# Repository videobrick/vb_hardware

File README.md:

hardware
========

OSHW Video Interface Hardware

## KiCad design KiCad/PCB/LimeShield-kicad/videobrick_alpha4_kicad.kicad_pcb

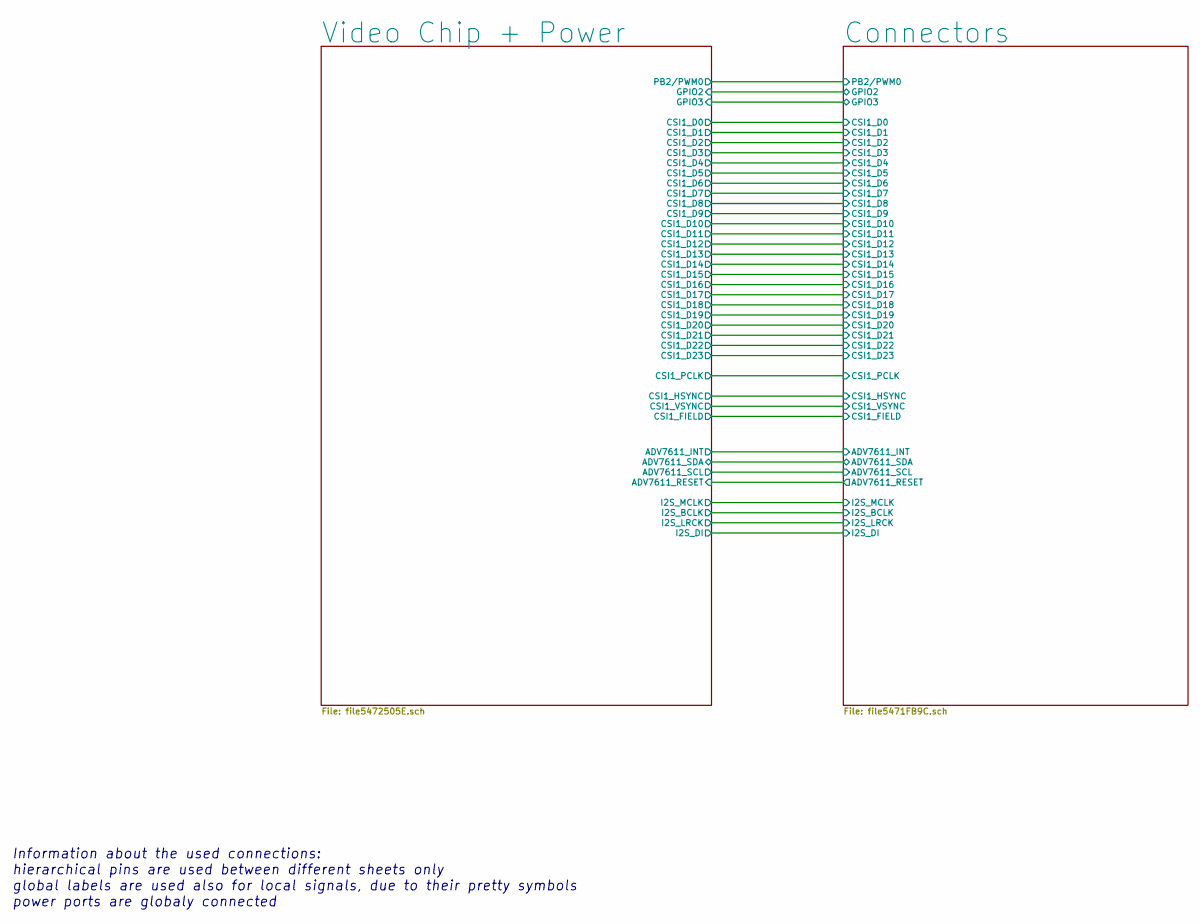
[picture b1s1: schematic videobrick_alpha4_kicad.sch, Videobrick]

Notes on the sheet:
Information about the used connections: hierarchical pins are used between different sheets only global labels are used also for local signals, due to their pretty symbols power ports are globaly connected

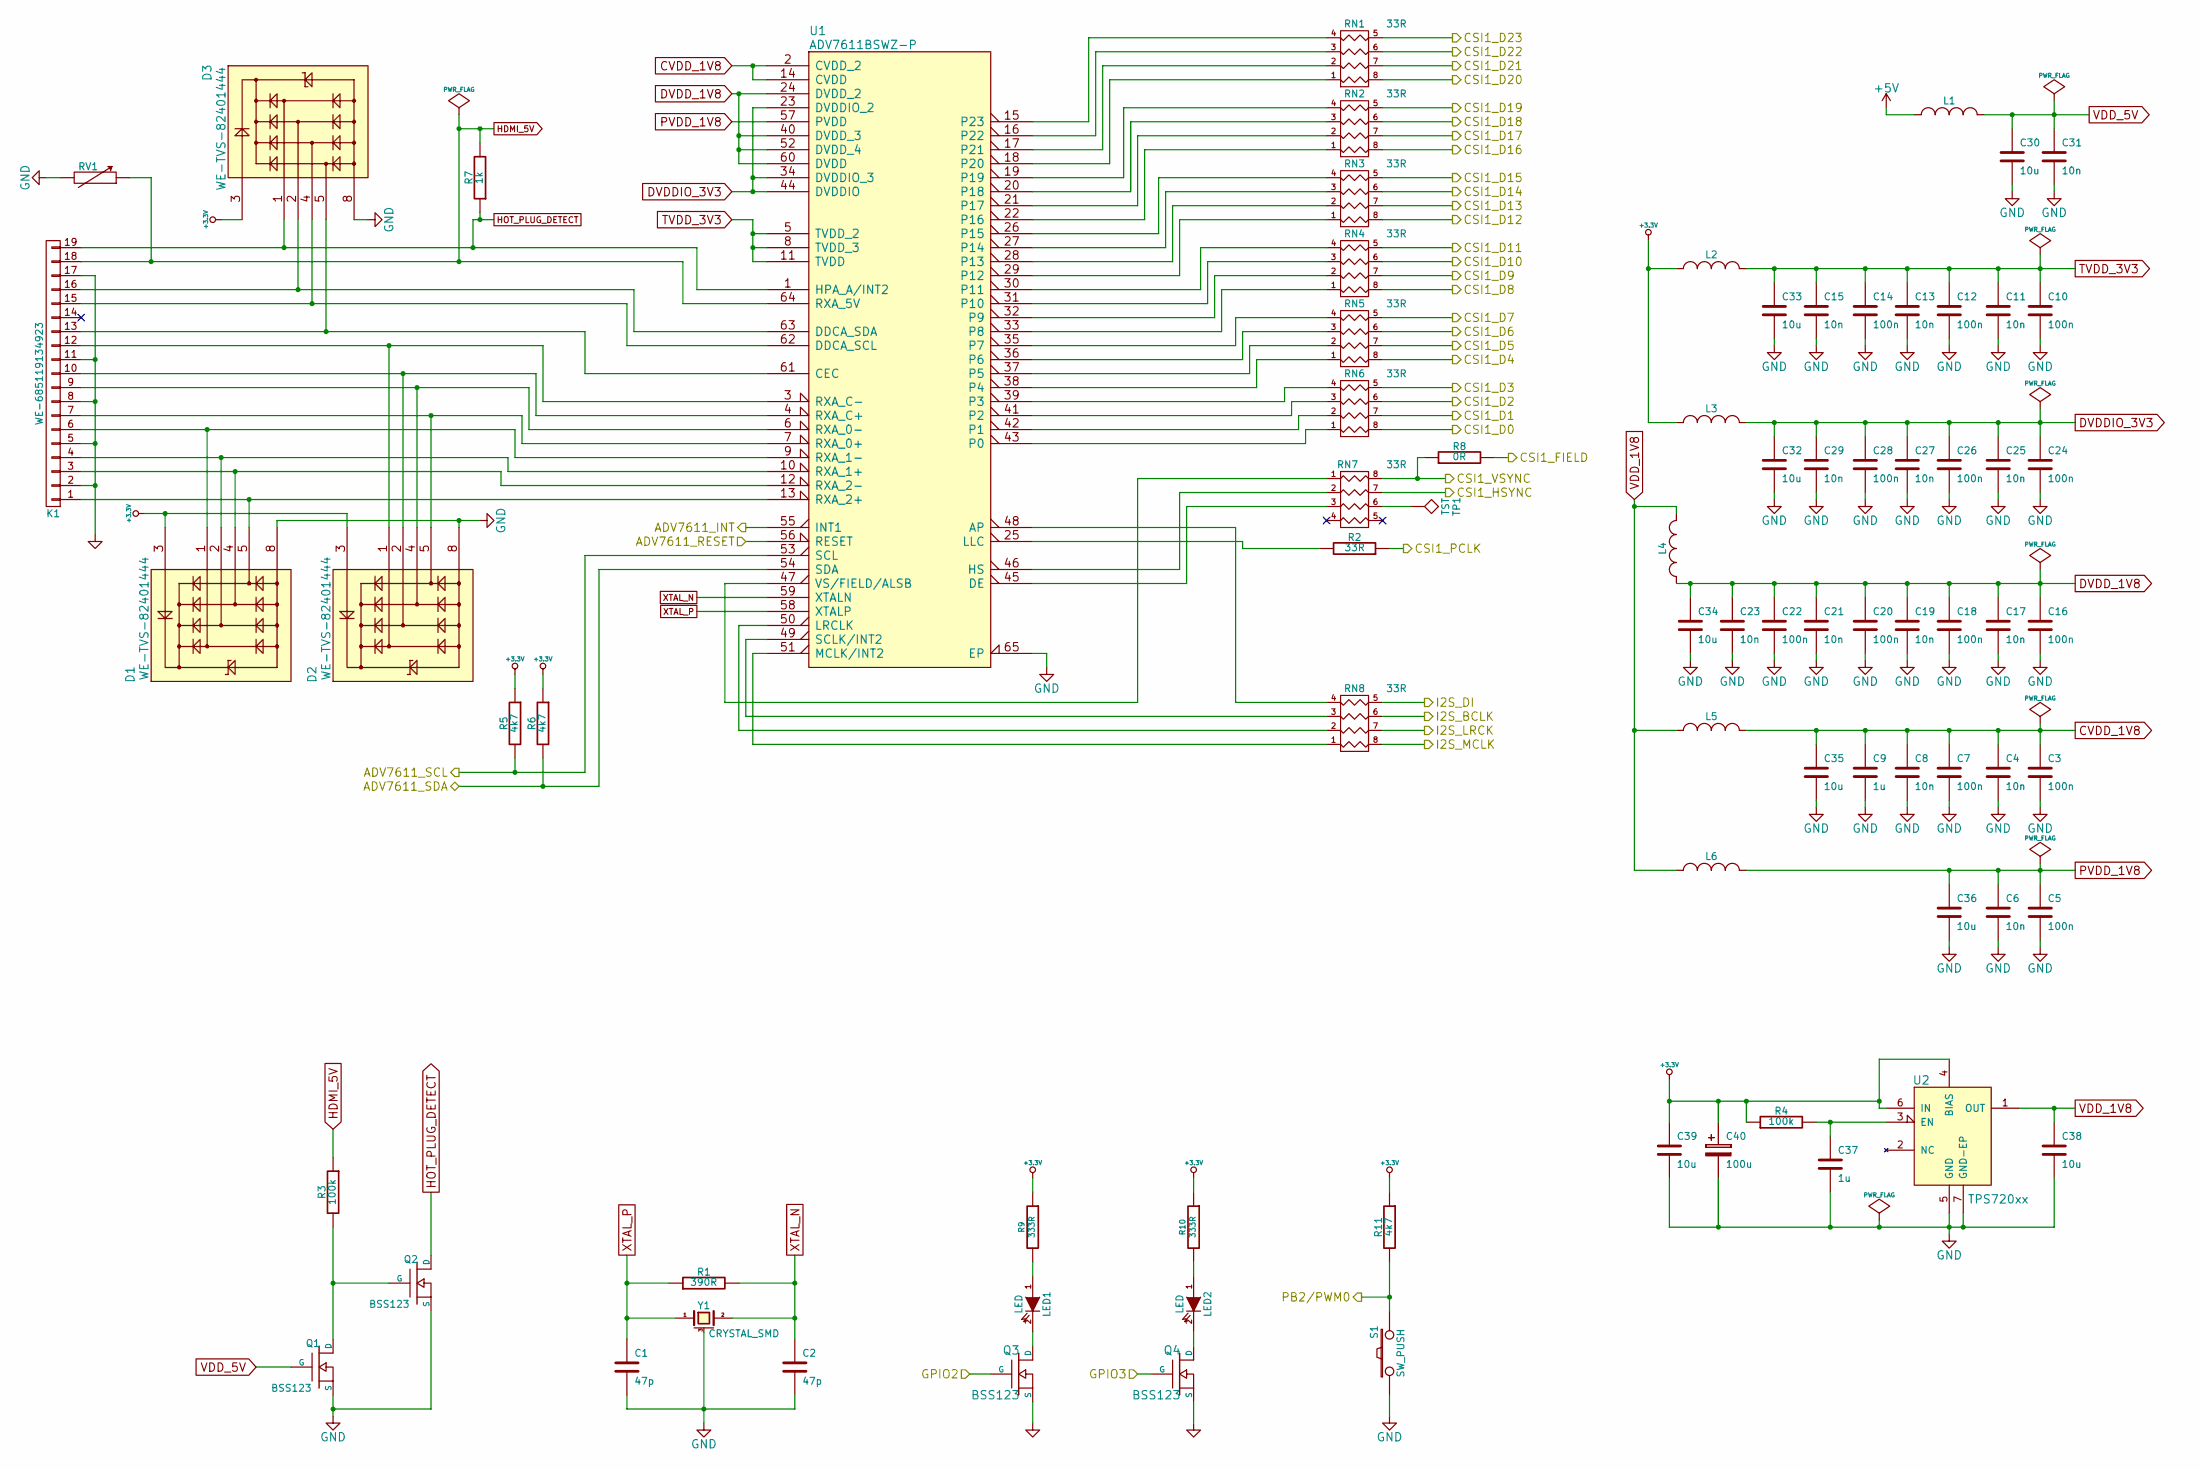
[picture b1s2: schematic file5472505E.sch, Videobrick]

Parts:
C1, C2: 47p; C_0402
C3, C5, C7, C10, C12, C14, C16, C18, C20, C22, C24, C26, C28: 100n; C_0402
C4, C6, C8, C11, C13, C15, C17, C19, C21, C23, C25, C27, C29, C31: 10n; C_0402
C9, C37: 1u; C_0603
C30, C32, C33, C34, C35, C36, C38, C39: 10u; C_0805
C40: 100u; RCL_153CLV-0405
D1, D2, D3: WE-TVS-82401444; WE-TVS_82401444_WE-TVS_MSOP-10L
K1: WE-685119134923; INPUTOUTPUTIO_685119134923
L1, L2, L3, L4, L5, L6: INDUCTOR_SMALL; WE-CBF_0805
LED1, LED2: LED; LED_CHIPLED_0805
Q1, Q2, Q3, Q4: BSS123; SOT-23-GDS
R1: 390R; R_0402
R2: 33R; R_0402
R3, R4: 100k; R_0402
R5, R6, R11: 4k7; R_0402
R7: 1k; R_0402
R8: 0R; R_0402
R9, R10: 333R; R_0402
RN1, RN2, RN3, RN4, RN5, RN6, RN7, RN8: 33R; RESISTOR-DIL_4X0402ARV341
RV1: RVAR; WE-VS_WESURGE_0402
S1: SW_PUSH; SPARKFUN-ELECTROMECHANICAL_TACTILE-PTH
TP1: TST; TESTPAD_TP06R
U1: ADV7611BSWZ-P; ADI-PHASE-2_QFP50P1200X1200X160-65N
U2: TPS720xx; TEXAS-INSTRUMENTS_BY_ELEMENT14_BATCH_1_SON65P200X200X80-7N
Y1: CRYSTAL_SMD; XTALS_5MM_3.2MM

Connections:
+3.3V: C39.1, C40.1, D1.3, D2.3, D3.3, L2.1, L3.1, R4.1, R5.1, R6.1, R9.1, R10.1, R11.1, U2.4 (BIAS), U2.6 (IN); also elsewhere on the board
+5V: L1.1; also elsewhere on the board
/Connectors/ADV7611_INT: U1.55 (INT1); also elsewhere on the board
/Connectors/ADV7611_RESET: U1.56 (RESET); also elsewhere on the board
/Connectors/ADV7611_SCL: R5.2, U1.53 (SCL); also elsewhere on the board
/Connectors/ADV7611_SDA: R6.2, U1.54 (SDA); also elsewhere on the board
/Connectors/CSI1_D0: RN6.8 (R1); also elsewhere on the board
/Connectors/CSI1_D1: RN6.7 (R2); also elsewhere on the board
/Connectors/CSI1_D2: RN6.6 (R3); also elsewhere on the board
/Connectors/CSI1_D3: RN6.5 (R4); also elsewhere on the board
/Connectors/CSI1_D4: RN5.8 (R1); also elsewhere on the board
/Connectors/CSI1_D5: RN5.7 (R2); also elsewhere on the board
/Connectors/CSI1_D6: RN5.6 (R3); also elsewhere on the board
/Connectors/CSI1_D7: RN5.5 (R4); also elsewhere on the board
/Connectors/CSI1_D8: RN4.8 (R1); also elsewhere on the board
/Connectors/CSI1_D9: RN4.7 (R2); also elsewhere on the board
/Connectors/CSI1_D10: RN4.6 (R3); also elsewhere on the board
/Connectors/CSI1_D11: RN4.5 (R4); also elsewhere on the board
/Connectors/CSI1_D12: RN3.8 (R1); also elsewhere on the board
/Connectors/CSI1_D13: RN3.7 (R2); also elsewhere on the board
/Connectors/CSI1_D14: RN3.6 (R3); also elsewhere on the board
/Connectors/CSI1_D15: RN3.5 (R4); also elsewhere on the board
/Connectors/CSI1_D16: RN2.8 (R1); also elsewhere on the board
/Connectors/CSI1_D17: RN2.7 (R2); also elsewhere on the board
/Connectors/CSI1_D18: RN2.6 (R3); also elsewhere on the board
/Connectors/CSI1_D19: RN2.5 (R4); also elsewhere on the board
/Connectors/CSI1_D20: RN1.8 (R1); also elsewhere on the board
/Connectors/CSI1_D21: RN1.7 (R2); also elsewhere on the board
/Connectors/CSI1_D22: RN1.6 (R3); also elsewhere on the board
/Connectors/CSI1_D23: RN1.5 (R4); also elsewhere on the board
/Connectors/CSI1_FIELD: R8.2; also elsewhere on the board
/Connectors/CSI1_HSYNC: RN7.7 (R2); also elsewhere on the board
/Connectors/CSI1_PCLK: R2.1; also elsewhere on the board
/Connectors/CSI1_VSYNC: R8.1, RN7.8 (R1); also elsewhere on the board
/Connectors/GPIO2: Q3.G; also elsewhere on the board
/Connectors/GPIO3: Q4.G; also elsewhere on the board
/Connectors/I2S_BCLK: RN8.6 (R3); also elsewhere on the board
/Connectors/I2S_DI: RN8.5 (R4); also elsewhere on the board
/Connectors/I2S_LRCK: RN8.7 (R2); also elsewhere on the board
/Connectors/I2S_MCLK: RN8.8 (R1); also elsewhere on the board
/Connectors/PB2/PWM0: R11.2, S1.2
CVDD_1V8: C3.1, C4.1, C7.1, C8.1, C9.1, C35.1, L5.2, U1.2 (CVDD_2), U1.14 (CVDD)
DVDDIO_3V3: C24.1, C25.1, C26.1, C27.1, C28.1, C29.1, C32.1, L3.2, U1.23 (DVDDIO_2), U1.34 (DVDDIO_3), U1.44 (DVDDIO)
DVDD_1V8: C16.1, C17.1, C18.1, C19.1, C20.1, C21.1, C22.1, C23.1, C34.1, L4.1, U1.24 (DVDD_2), U1.40 (DVDD_3), U1.52 (DVDD_4), U1.60 (DVDD)
GND: C1.2, C2.2, C3.2, C4.2, C5.2, C6.2, C7.2, C8.2, C9.2, C10.2, C11.2, C12.2, C13.2, C14.2, C15.2, C16.2, C17.2, C18.2, C19.2, C20.2, C21.2, C22.2, C23.2, C24.2, C25.2, C26.2, C27.2, C28.2, C29.2, C30.2, C31.2, C32.2, C33.2, C34.2, C35.2, C36.2, C37.2, C38.2, C39.2, C40.2, D1.8, D2.8, D3.8, K1.2, K1.5, K1.8, K1.11, K1.17, Q1.S, Q2.S, Q3.S, Q4.S, RV1.2, S1.1, U1.65 (EP), U2.5 (GND), U2.7 (GND-EP), Y1.3 (case); also elsewhere on the board
HDMI_5V: K1.18, R3.1, R7.2, RV1.1, U1.64 (RXA_5V)
HOT_PLUG_DETECT: D3.1, K1.19, Q2.D, R7.1, U1.1 (HPA_A/INT2)
unnamed: C37.1, R4.2, U2.3 (EN)
unnamed: D1.1, K1.6, U1.9 (RXA_1-)
unnamed: D1.2, K1.4, U1.10 (RXA_1+)
unnamed: D1.4, K1.3, U1.12 (RXA_2-)
unnamed: D1.5, K1.1, U1.13 (RXA_2+)
unnamed: D2.1, K1.12, U1.3 (RXA_C-)
unnamed: D2.2, K1.10, U1.4 (RXA_C+)
unnamed: D2.4, K1.9, U1.6 (RXA_0-)
unnamed: D2.5, K1.7, U1.7 (RXA_0+)
unnamed: D3.2, K1.16, U1.63 (DDCA_SDA)
unnamed: D3.4, K1.15, U1.62 (DDCA_SCL)
unnamed: D3.5, K1.13, U1.61 (CEC)
unnamed: LED1.1 (A), R9.2
unnamed: LED1.2 (K), Q3.D
unnamed: LED2.1 (A), R10.2
unnamed: LED2.2 (K), Q4.D
unnamed: Q1.D, Q2.G, R3.2
unnamed: R2.2, U1.25 (LLC)
unnamed: RN1.1, U1.18 (P20)
unnamed: RN1.2, U1.17 (P21)
unnamed: RN1.3, U1.16 (P22)
unnamed: RN1.4, U1.15 (P23)
unnamed: RN2.1, U1.22 (P16)
unnamed: RN2.2, U1.21 (P17)
unnamed: RN2.3, U1.20 (P18)
unnamed: RN2.4, U1.19
unnamed: RN3.1, U1.29 (P12)
unnamed: RN3.2, U1.28 (P13)
unnamed: RN3.3, U1.27 (P14)
unnamed: RN3.4, U1.26 (P15)
unnamed: RN4.1, U1.33 (P8)
unnamed: RN4.2, U1.32 (P9)
unnamed: RN4.3, U1.31 (P10)
unnamed: RN4.4, U1.30 (P11)
unnamed: RN5.1, U1.38 (P4)
unnamed: RN5.2, U1.37 (P5)
unnamed: RN5.3, U1.36 (P6)
unnamed: RN5.4, U1.35 (P7)
unnamed: RN6.1, U1.43 (P0)
unnamed: RN6.2, U1.42 (P1)
unnamed: RN6.3, U1.41 (P2)
unnamed: RN6.4, U1.39 (P3)
unnamed: RN7.1, U1.47 (VS/FIELD/ALSB)
unnamed: RN7.2, U1.46 (HS)
unnamed: RN7.3, U1.45 (DE)
unnamed: RN7.6 (R3), TP1.1
unnamed: RN8.1, U1.51 (MCLK/INT2)
unnamed: RN8.2, U1.50 (LRCLK)
unnamed: RN8.3, U1.49 (SCLK/INT2)
unnamed: RN8.4, U1.48 (AP)
PVDD_1V8: C5.1, C6.1, C36.1, L6.2, U1.57 (PVDD)
TVDD_3V3: C10.1, C11.1, C12.1, C13.1, C14.1, C15.1, C33.1, L2.2, U1.5 (TVDD_2), U1.8 (TVDD_3), U1.11 (TVDD)
VDD_1V8: C38.1, L4.2, L5.1, L6.1, U2.1 (OUT)
VDD_5V: C30.1, C31.1, L1.2, Q1.G
XTAL_N: C2.1, R1.2, U1.59 (XTALN), Y1.2
XTAL_P: C1.1, R1.1, U1.58 (XTALP), Y1.1

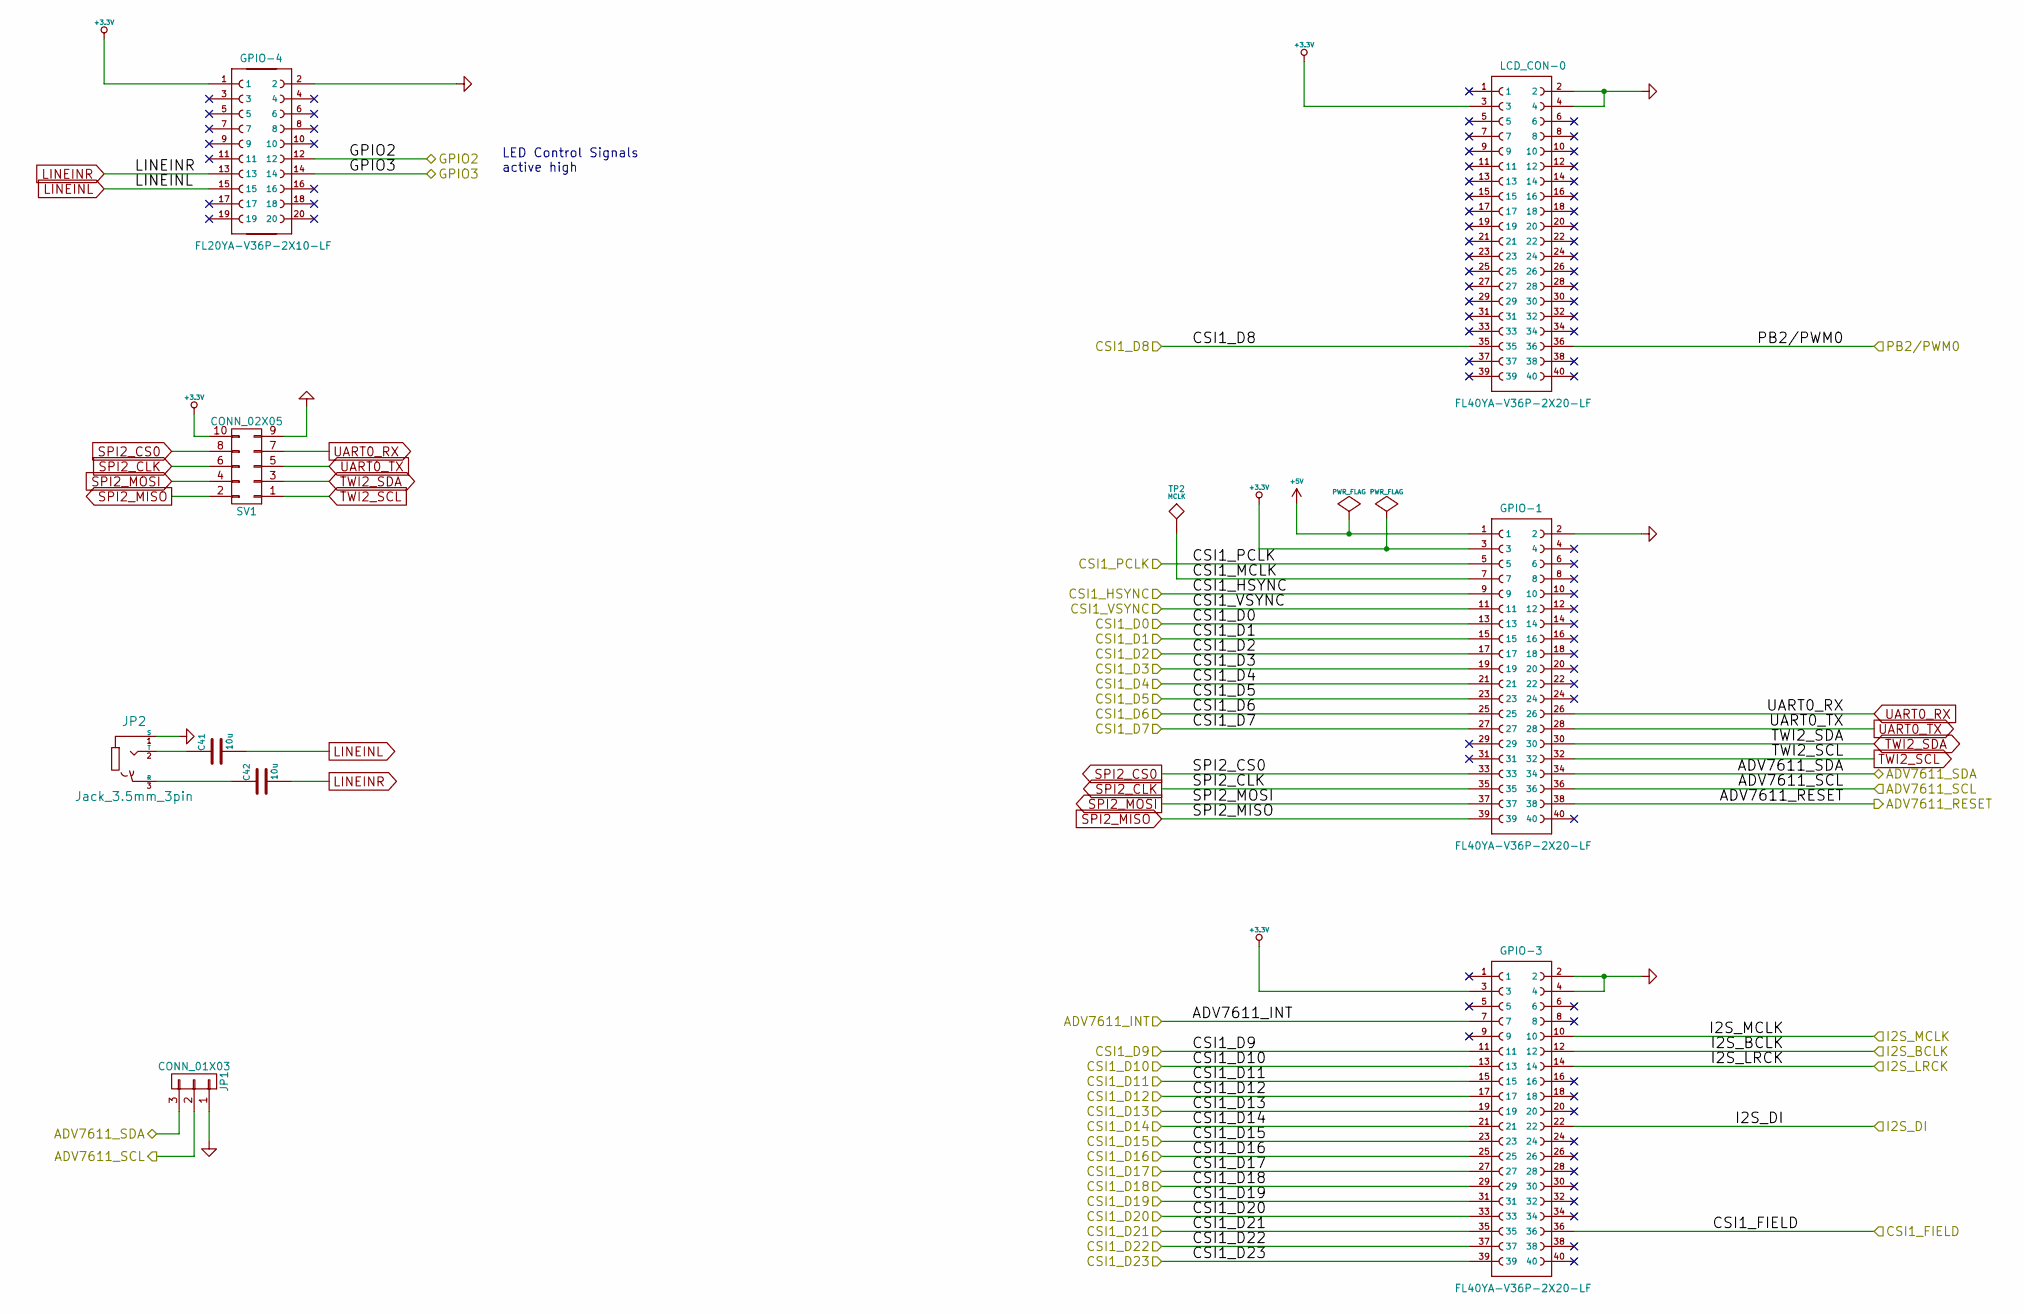
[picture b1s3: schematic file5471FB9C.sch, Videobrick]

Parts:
C41, C42: 10u; C_0805
GPIO-1, GPIO-3: FL40YA-V36P-2X20-LF
GPIO-4: FL20YA-V36P-2X10-LF
JP1: CONN_01X03; JUMPER_JP2
JP2: Jack_3.5mm_3pin; SPARKFUN-CONNECTORS_AUDIO-JACK
LCD_CON-0: FL40YA-V36P-2X20-LF
SV1: CONN_02X05; CON-LSTB_MA05-2
TP2: MCLK; TESTPAD_TP06R

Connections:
+3.3V: GPIO-1.3, GPIO-3.3, GPIO-4.1, LCD_CON-0.3, SV1.10; also elsewhere on the board
+5V: GPIO-1.1; also elsewhere on the board
/Connectors/ADV7611_INT: GPIO-3.7; also elsewhere on the board
/Connectors/ADV7611_RESET: GPIO-1.38; also elsewhere on the board
/Connectors/ADV7611_SCL: GPIO-1.36, JP1.2; also elsewhere on the board
/Connectors/ADV7611_SDA: GPIO-1.34, JP1.3; also elsewhere on the board
/Connectors/CSI1_D0: GPIO-1.13; also elsewhere on the board
/Connectors/CSI1_D1: GPIO-1.15; also elsewhere on the board
/Connectors/CSI1_D2: GPIO-1.17; also elsewhere on the board
/Connectors/CSI1_D3: GPIO-1.19; also elsewhere on the board
/Connectors/CSI1_D4: GPIO-1.21; also elsewhere on the board
/Connectors/CSI1_D5: GPIO-1.23; also elsewhere on the board
/Connectors/CSI1_D6: GPIO-1.25; also elsewhere on the board
/Connectors/CSI1_D7: GPIO-1.27; also elsewhere on the board
/Connectors/CSI1_D9: GPIO-3.11; also elsewhere on the board
/Connectors/CSI1_D10: GPIO-3.13; also elsewhere on the board
/Connectors/CSI1_D11: GPIO-3.15; also elsewhere on the board
/Connectors/CSI1_D12: GPIO-3.17; also elsewhere on the board
/Connectors/CSI1_D13: GPIO-3.19; also elsewhere on the board
/Connectors/CSI1_D14: GPIO-3.21; also elsewhere on the board
/Connectors/CSI1_D15: GPIO-3.23; also elsewhere on the board
/Connectors/CSI1_D16: GPIO-3.25; also elsewhere on the board
/Connectors/CSI1_D17: GPIO-3.27; also elsewhere on the board
/Connectors/CSI1_D18: GPIO-3.29; also elsewhere on the board
/Connectors/CSI1_D19: GPIO-3.31; also elsewhere on the board
/Connectors/CSI1_D20: GPIO-3.33; also elsewhere on the board
/Connectors/CSI1_D21: GPIO-3.35; also elsewhere on the board
/Connectors/CSI1_D22: GPIO-3.37; also elsewhere on the board
/Connectors/CSI1_D23: GPIO-3.39; also elsewhere on the board
/Connectors/CSI1_FIELD: GPIO-3.36; also elsewhere on the board
/Connectors/CSI1_HSYNC: GPIO-1.9; also elsewhere on the board
/Connectors/CSI1_MCLK: GPIO-1.7, TP2.1
/Connectors/CSI1_PCLK: GPIO-1.5; also elsewhere on the board
/Connectors/CSI1_VSYNC: GPIO-1.11; also elsewhere on the board
/Connectors/GPIO2: GPIO-4.12; also elsewhere on the board
/Connectors/GPIO3: GPIO-4.14; also elsewhere on the board
/Connectors/I2S_BCLK: GPIO-3.12; also elsewhere on the board
/Connectors/I2S_DI: GPIO-3.22; also elsewhere on the board
/Connectors/I2S_LRCK: GPIO-3.14; also elsewhere on the board
/Connectors/I2S_MCLK: GPIO-3.10; also elsewhere on the board
GND: GPIO-1.2, GPIO-3.2, GPIO-3.4, GPIO-4.2, JP1.1, JP2.1 (S), LCD_CON-0.2, LCD_CON-0.4, SV1.9; also elsewhere on the board
LINEINL: C41.2, GPIO-4.15
LINEINR: C42.2, GPIO-4.13
unnamed: C41.1, JP2.2 (T)
unnamed: C42.1, JP2.3 (R)
SPI2_CLK: GPIO-1.35, SV1.6
SPI2_CS0: GPIO-1.33, SV1.8
SPI2_MISO: GPIO-1.39, SV1.2
SPI2_MOSI: GPIO-1.37, SV1.4
TWI2_SCL: GPIO-1.32, SV1.1
TWI2_SDA: GPIO-1.30, SV1.3
UART0_RX: GPIO-1.26, SV1.7
UART0_TX: GPIO-1.28, SV1.5

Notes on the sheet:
LED Control Signals active high

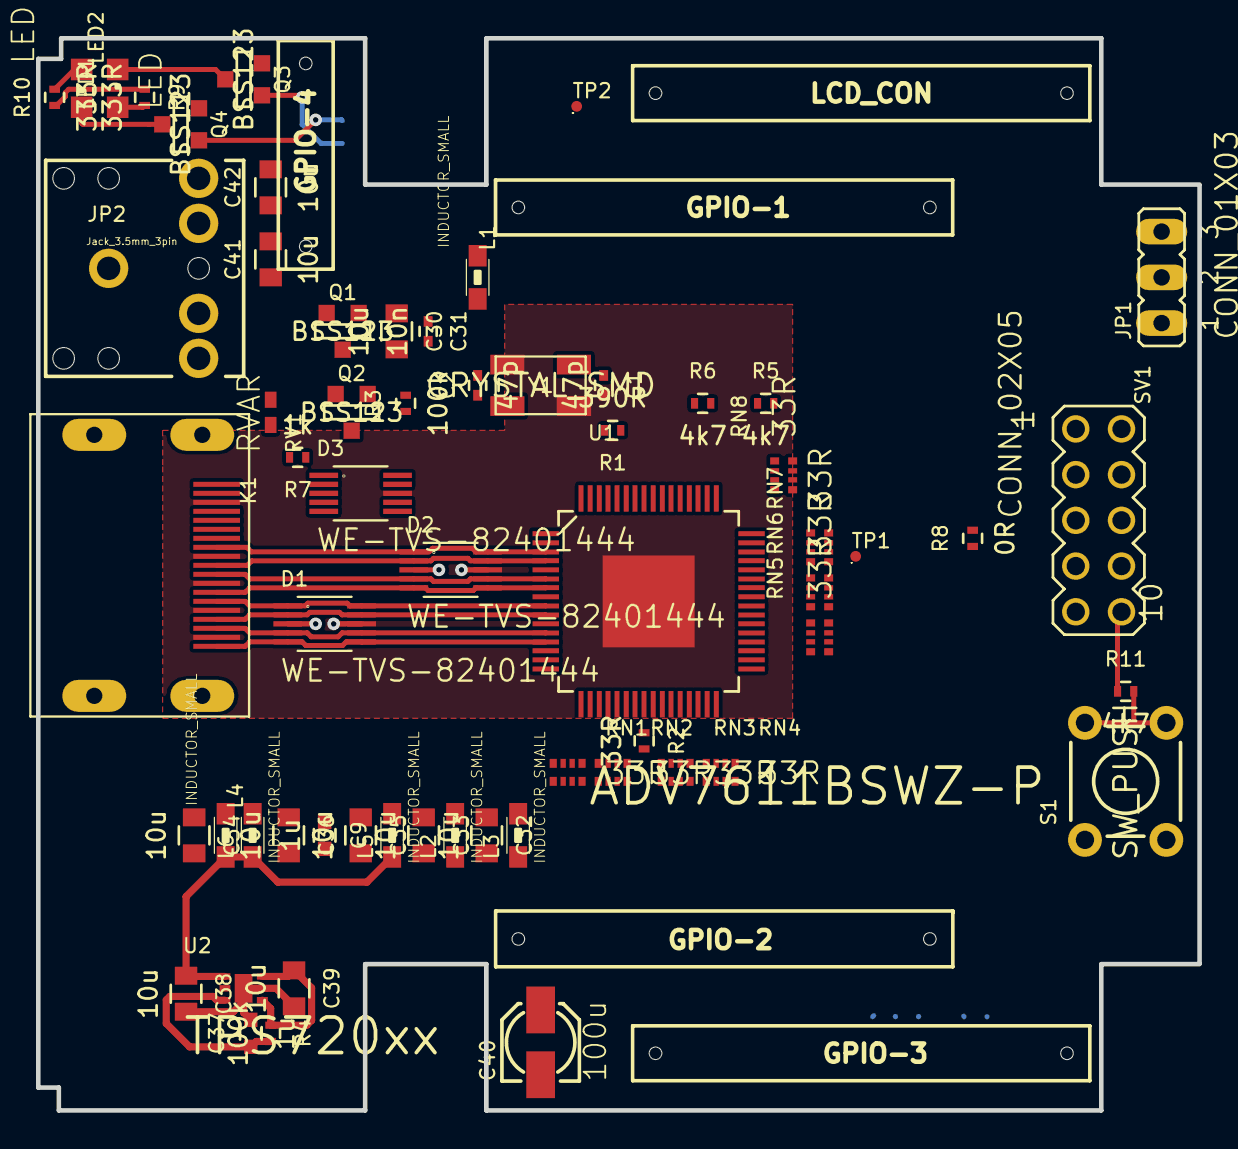
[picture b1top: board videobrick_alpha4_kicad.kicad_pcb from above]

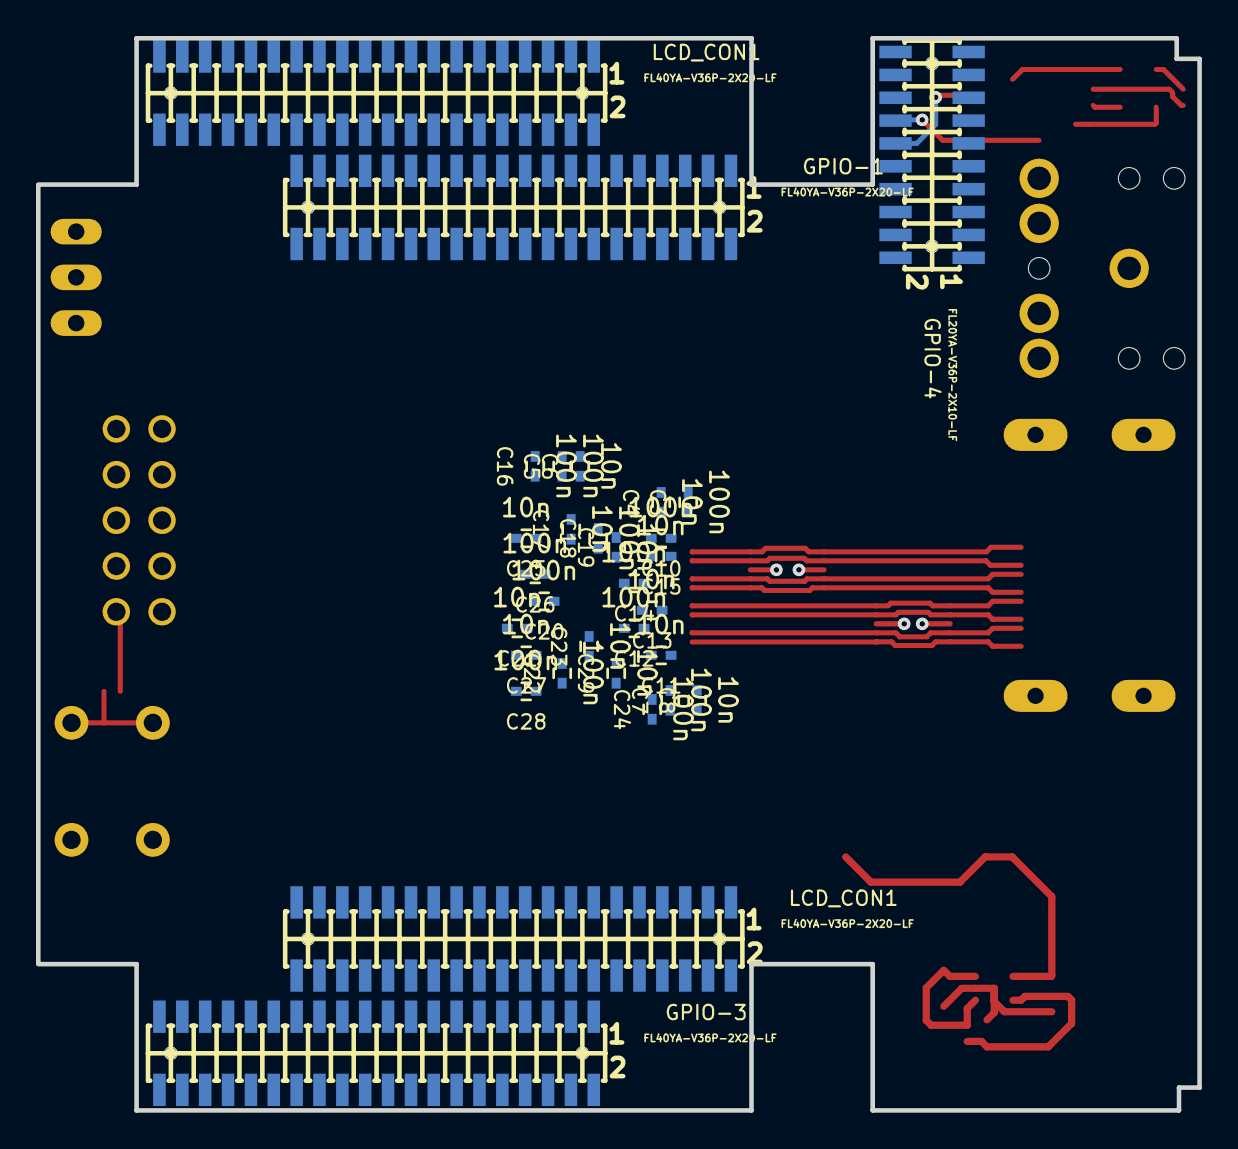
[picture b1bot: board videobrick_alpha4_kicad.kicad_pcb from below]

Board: 4 copper layers, 64.5 x 59.6 mm, 92 parts (31 on the bottom side), 116 nets.

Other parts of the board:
LCD_CON1, LCD_CON1#2: FL40YA-V36P-2X20-LF; A10_OLIMEXINO_LIME_SHIELD_1-YA-V36P-2X20-LF

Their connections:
+3.3V: LCD_CON1.3; also elsewhere on the board
+5V: LCD_CON1.1; also elsewhere on the board
/Connectors/CSI1_D8: LCD_CON1.35; also elsewhere on the board
GND: LCD_CON1.2, LCD_CON1.4; also elsewhere on the board

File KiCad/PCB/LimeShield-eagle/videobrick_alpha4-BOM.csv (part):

"Part";"Value";"Device";"Package";"Description";"MF";"MPN";"OC_FARNELL";"OC_NEWARK";"PACKAGE";"SUPPLIER";"TP_SIGNAL_NAME";
"C1";"47pF";"C-EUC0402";"C0402";"CAPACITOR, European symbol";"";"";"";"";"";"";"";
"C2";"47pF";"C-EUC0402";"C0402";"CAPACITOR, European symbol";"";"";"";"";"";"";"";
"C3";"100nF";"C-EUC0402";"C0402";"CAPACITOR, European symbol";"";"";"";"";"";"";"";
"C4";"10nF";"C-EUC0402";"C0402";"CAPACITOR, European symbol";"";"";"";"";"";"";"";
"C5";"100nF";"C-EUC0402";"C0402";"CAPACITOR, European symbol";"";"";"";"";"";"";"";
"C6";"10nF";"C-EUC0402";"C0402";"CAPACITOR, European symbol";"";"";"";"";"";"";"";
"C7";"100nF";"C-EUC0402";"C0402";"CAPACITOR, European symbol";"";"";"";"";"";"";"";
"C8";"10nF";"C-EUC0402";"C0402";"CAPACITOR, European symbol";"";"";"";"";"";"";"";
"C9";"1uF";"C-EUC0603";"C0603";"CAPACITOR, European symbol";"";"";"";"";"";"";"";
"C10";"100nF";"C-EUC0402";"C0402";"CAPACITOR, European symbol";"";"";"";"";"";"";"";
"C11";"10nF";"C-EUC0402";"C0402";"CAPACITOR, European symbol";"";"";"";"";"";"";"";
"C12";"100nF";"C-EUC0402";"C0402";"CAPACITOR, European symbol";"";"";"";"";"";"";"";
"C13";"10nF";"C-EUC0402";"C0402";"CAPACITOR, European symbol";"";"";"";"";"";"";"";
"C14";"100nF";"C-EUC0402";"C0402";"CAPACITOR, European symbol";"";"";"";"";"";"";"";
"C15";"10nF";"C-EUC0402";"C0402";"CAPACITOR, European symbol";"";"";"";"";"";"";"";
"C16";"100nF";"C-EUC0402";"C0402";"CAPACITOR, European symbol";"";"";"";"";"";"";"";
"C17";"10nF";"C-EUC0402";"C0402";"CAPACITOR, European symbol";"";"";"";"";"";"";"";
"C18";"100nF";"C-EUC0402";"C0402";"CAPACITOR, European symbol";"";"";"";"";"";"";"";
"C19";"10nF";"C-EUC0402";"C0402";"CAPACITOR, European symbol";"";"";"";"";"";"";"";
"C20";"100nF";"C-EUC0402";"C0402";"CAPACITOR, European symbol";"";"";"";"";"";"";"";
"C21";"10nF";"C-EUC0402";"C0402";"CAPACITOR, European symbol";"";"";"";"";"";"";"";
"C22";"100nF";"C-EUC0402";"C0402";"CAPACITOR, European symbol";"";"";"";"";"";"";"";
"C23";"10nF";"C-EUC0402";"C0402";"CAPACITOR, European symbol";"";"";"";"";"";"";"";
"C24";"100nF";"C-EUC0402";"C0402";"CAPACITOR, European symbol";"";"";"";"";"";"";"";
"C25";"10nF";"C-EUC0402";"C0402";"CAPACITOR, European symbol";"";"";"";"";"";"";"";
"C26";"100nF";"C-EUC0402";"C0402";"CAPACITOR, European symbol";"";"";"";"";"";"";"";
"C27";"10nF";"C-EUC0402";"C0402";"CAPACITOR, European symbol";"";"";"";"";"";"";"";
"C28";"100nF";"C-EUC0402";"C0402";"CAPACITOR, European symbol";"";"";"";"";"";"";"";
"C29";"10nF";"C-EUC0402";"C0402";"CAPACITOR, European symbol";"";"";"";"";"";"";"";
"C30";"10uF";"C-EUC0805";"C0805";"CAPACITOR, European symbol";"";"";"";"";"";"";"";
"C31";"10nF";"C-EUC0402";"C0402";"CAPACITOR, European symbol";"";"";"";"";"";"";"";
"C32";"10uF";"C-EUC0805";"C0805";"CAPACITOR, European symbol";"";"";"";"";"";"";"";
"C33";"10uF";"C-EUC0805";"C0805";"CAPACITOR, European symbol";"";"";"";"";"";"";"";
"C34";"10uF";"C-EUC0805";"C0805";"CAPACITOR, European symbol";"";"";"";"";"";"";"";
"C35";"10uF";"C-EUC0805";"C0805";"CAPACITOR, European symbol";"";"";"";"";"";"";"";
"C36";"10uF";"C-EUC0805";"C0805";"CAPACITOR, European symbol";"";"";"";"";"";"";"";
"C37";"1uF";"C-EUC0603";"C0603";"CAPACITOR, European symbol";"";"";"";"";"";"";"";
"C38";"10uF";"C-EUC0805";"C0805";"CAPACITOR, European symbol";"";"";"";"";"";"";"";
"C39";"10uF";"C-EUC0805";"C0805";"CAPACITOR, European symbol";"";"";"";"";"";"";"";
"C40";"100uF";"CPOL-EU153CLV-0405";"153CLV-0405";"POLARIZED CAPACITOR, European symbol";"";"";"";"";"";"";"";
"C41";"10uF";"C-EUC0805";"C0805";"CAPACITOR, European symbol";"";"";"";"";"";"";"";
"C42";"10uF";"C-EUC0805";"C0805";"CAPACITOR, European symbol";"";"";"";"";"";"";"";
"CON1";"A10_OLINUXINO_LIME_SHIELD_TEMPLATE";"A10_OLINUXINO_LIME_SHIELD_TEMPLATE";"A10_OLINUXINO_LIME_SHIELD";"";"";"";"";"";"";"";"";
"D1";"";"WE-TVS_82401444";"WE-TVS_MSOP-10L";"TVS Diode Array WE-TVS, Super Speed Serie";"";"82401444";"1825863";"79R6952";"MSOP-10L";"Wuerth Elektronik";"";
"D2";"";"WE-TVS_82401444";"WE-TVS_MSOP-10L";"TVS Diode Array WE-TVS, Super Speed Serie";"";"82401444";"1825863";"79R6952";"MSOP-10L";"Wuerth Elektronik";"";
"D3";"";"WE-TVS_82401444";"WE-TVS_MSOP-10L";"TVS Diode Array WE-TVS, Super Speed Serie";"";"82401444";"1825863";"79R6952";"MSOP-10L";"Wuerth Elektronik";"";
"FID1";"FIDUCIALUFIDUCIAL";"FIDUCIALUFIDUCIAL";"MICRO-FIDUCIAL";"Fiducial Alignment Points";"";"";"";"";"";"";"";
"FID2";"FIDUCIAL1X2";"FIDUCIAL1X2";"FIDUCIAL-1X2";"Fiducial Alignment Points";"";"";"";"";"";"";"";
"JP1";"";"JP2E";"JP2";"JUMPER";"";"";"";"";"";"";"";
"JP2";"";"AUDIO-JACKPTH";"AUDIO-JACK";"3.5mm Audio Jack";"";"";"";"";"";"";"";
"K1";"685119134923";"685119134923";"685119134923";"WR-COM SMT Horizontal HDMI, 19 pins";"";"";"";"";"";"";"";
"L1";"";"WE-CBF-742792040_0805";"0805";"SMD EMI Suppression Ferrite Beads WE-CBF";"";"742792040";"1635735";"08P2371";"IND-0805";"Wuerth Elektronik";"";
"L2";"";"WE-CBF-742792040_0805";"0805";"SMD EMI Suppression Ferrite Beads WE-CBF";"";"742792040";"1635735";"08P2371";"IND-0805";"Wuerth Elektronik";"";
"L3";"";"WE-CBF-742792040_0805";"0805";"SMD EMI Suppression Ferrite Beads WE-CBF";"";"742792040";"1635735";"08P2371";"IND-0805";"Wuerth Elektronik";"";
"L4";"";"WE-CBF-742792040_0805";"0805";"SMD EMI Suppression Ferrite Beads WE-CBF";"";"742792040";"1635735";"08P2371";"IND-0805";"Wuerth Elektronik";"";
"L5";"";"WE-CBF-742792040_0805";"0805";"SMD EMI Suppression Ferrite Beads WE-CBF";"";"742792040";"1635735";"08P2371";"IND-0805";"Wuerth Elektronik";"";
"L6";"";"WE-CBF-742792040_0805";"0805";"SMD EMI Suppression Ferrite Beads WE-CBF";"";"742792040";"1635735";"08P2371";"IND-0805";"Wuerth Elektronik";"";
"LED1";"";"LEDCHIPLED_0805";"CHIPLED_0805";"LED";"";"";"";"";"";"";"";
"LED2";"";"LEDCHIPLED_0805";"CHIPLED_0805";"LED";"";"";"";"";"";"";"";
"LOGO1";"OSHW-LOGOL";"OSHW-LOGOL";"OSHW-LOGO-L";"Open Source Hardware Logo This logo indicates the piece of hardware it is found on incorporates a OSHW license and/or adheres to the definition of open source hardware found here: http://freedomdefined.org/OSHW";"";"";"";"";"";"";"";
"Q1";"BSS123";"BSS123";"SOT23";"N-CHANNEL MOS FET";"";"";"";"";"";"";"";
"Q2";"BSS123";"BSS123";"SOT23";"N-CHANNEL MOS FET";"";"";"";"";"";"";"";
"Q3";"BSS123";"BSS123";"SOT23";"N-CHANNEL MOS FET";"";"";"";"";"";"";"";
"Q4";"BSS123";"BSS123";"SOT23";"N-CHANNEL MOS FET";"";"";"";"";"";"";"";
"R1";"390R";"R-EU_R0402";"R0402";"RESISTOR, European symbol";"";"";"";"";"";"";"";
"R2";"33R";"R-EU_R0402";"R0402";"RESISTOR, European symbol";"";"";"";"";"";"";"";
"R3";"100k";"R-EU_R0402";"R0402";"RESISTOR, European symbol";"";"";"";"";"";"";"";
"R4";"100k";"R-EU_R0402";"R0402";"RESISTOR, European symbol";"";"";"";"";"";"";"";
"R5";"4k7";"R-EU_R0402";"R0402";"RESISTOR, European symbol";"";"";"";"";"";"";"";
"R6";"4k7";"R-EU_R0402";"R0402";"RESISTOR, European symbol";"";"";"";"";"";"";"";
"R7";"1k";"R-EU_R0402";"R0402";"RESISTOR, European symbol";"";"";"";"";"";"";"";
"R8";"0R";"R-EU_R0402";"R0402";"RESISTOR, European symbol";"";"";"";"";"";"";"";
"R9";"330R";"R-EU_R0402";"R0402";"RESISTOR, European symbol";"";"";"";"";"";"";"";
"R10";"330R";"R-EU_R0402";"R0402";"RESISTOR, European symbol";"";"";"";"";"";"";"";
"R11";"4k7";"R-EU_R0402";"R0402";"RESISTOR, European symbol";"";"";"";"";"";"";"";
"RN1";"33R";"4R-N0402ARV341";"4X0402ARV341";"Array Chip Resistor";"";"";"unknown";"unknown";"";"";"";
"RN2";"33R";"4R-N0402ARV341";"4X0402ARV341";"Array Chip Resistor";"";"";"unknown";"unknown";"";"";"";
"RN3";"33R";"4R-N0402ARV341";"4X0402ARV341";"Array Chip Resistor";"";"";"unknown";"unknown";"";"";"";
"RN4";"33R";"4R-N0402ARV341";"4X0402ARV341";"Array Chip Resistor";"";"";"unknown";"unknown";"";"";"";
"RN5";"33R";"4R-N0402ARV341";"4X0402ARV341";"Array Chip Resistor";"";"";"unknown";"unknown";"";"";"";
"RN6";"33R";"4R-N0402ARV341";"4X0402ARV341";"Array Chip Resistor";"";"";"unknown";"unknown";"";"";"";
"RN7";"33R";"4R-N0402ARV341";"4X0402ARV341";"Array Chip Resistor";"";"";"unknown";"unknown";"";"";"";
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
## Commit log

2014-09-18 added Alpha3 of LimeShield PCB
2014-09-24 version die bestellt wird
2014-10-16 added overview diagramm
2015-02-06 added KiCad-Design
